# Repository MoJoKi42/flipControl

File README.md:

# flipControl
Full controller for **BROSE** and **LAWO FlipDot** panels based on STM32 µC. Controllable via RS232, RS485 or 3.3V Serial.
With the DIP switches you can decide between BROSE / LAWO and set more parameters without reprogramming.

<ins>Software/µC:</ins>
- **STM32F103C8Tx** / BluePill Dev-Board
- CubeMX and HAL Libs
- "compile_and_flash.sh" to complile and flash µC under Linux

<ins>Hardware/PCB:</ins>
- PCB + Circuit made with EAGLE 6.6.0
- Gerber Files are in "Gerber.zip"

Picture of the finished board with soldered RS323 interface:

Two different font types are possible (if you render the text with the MCU):

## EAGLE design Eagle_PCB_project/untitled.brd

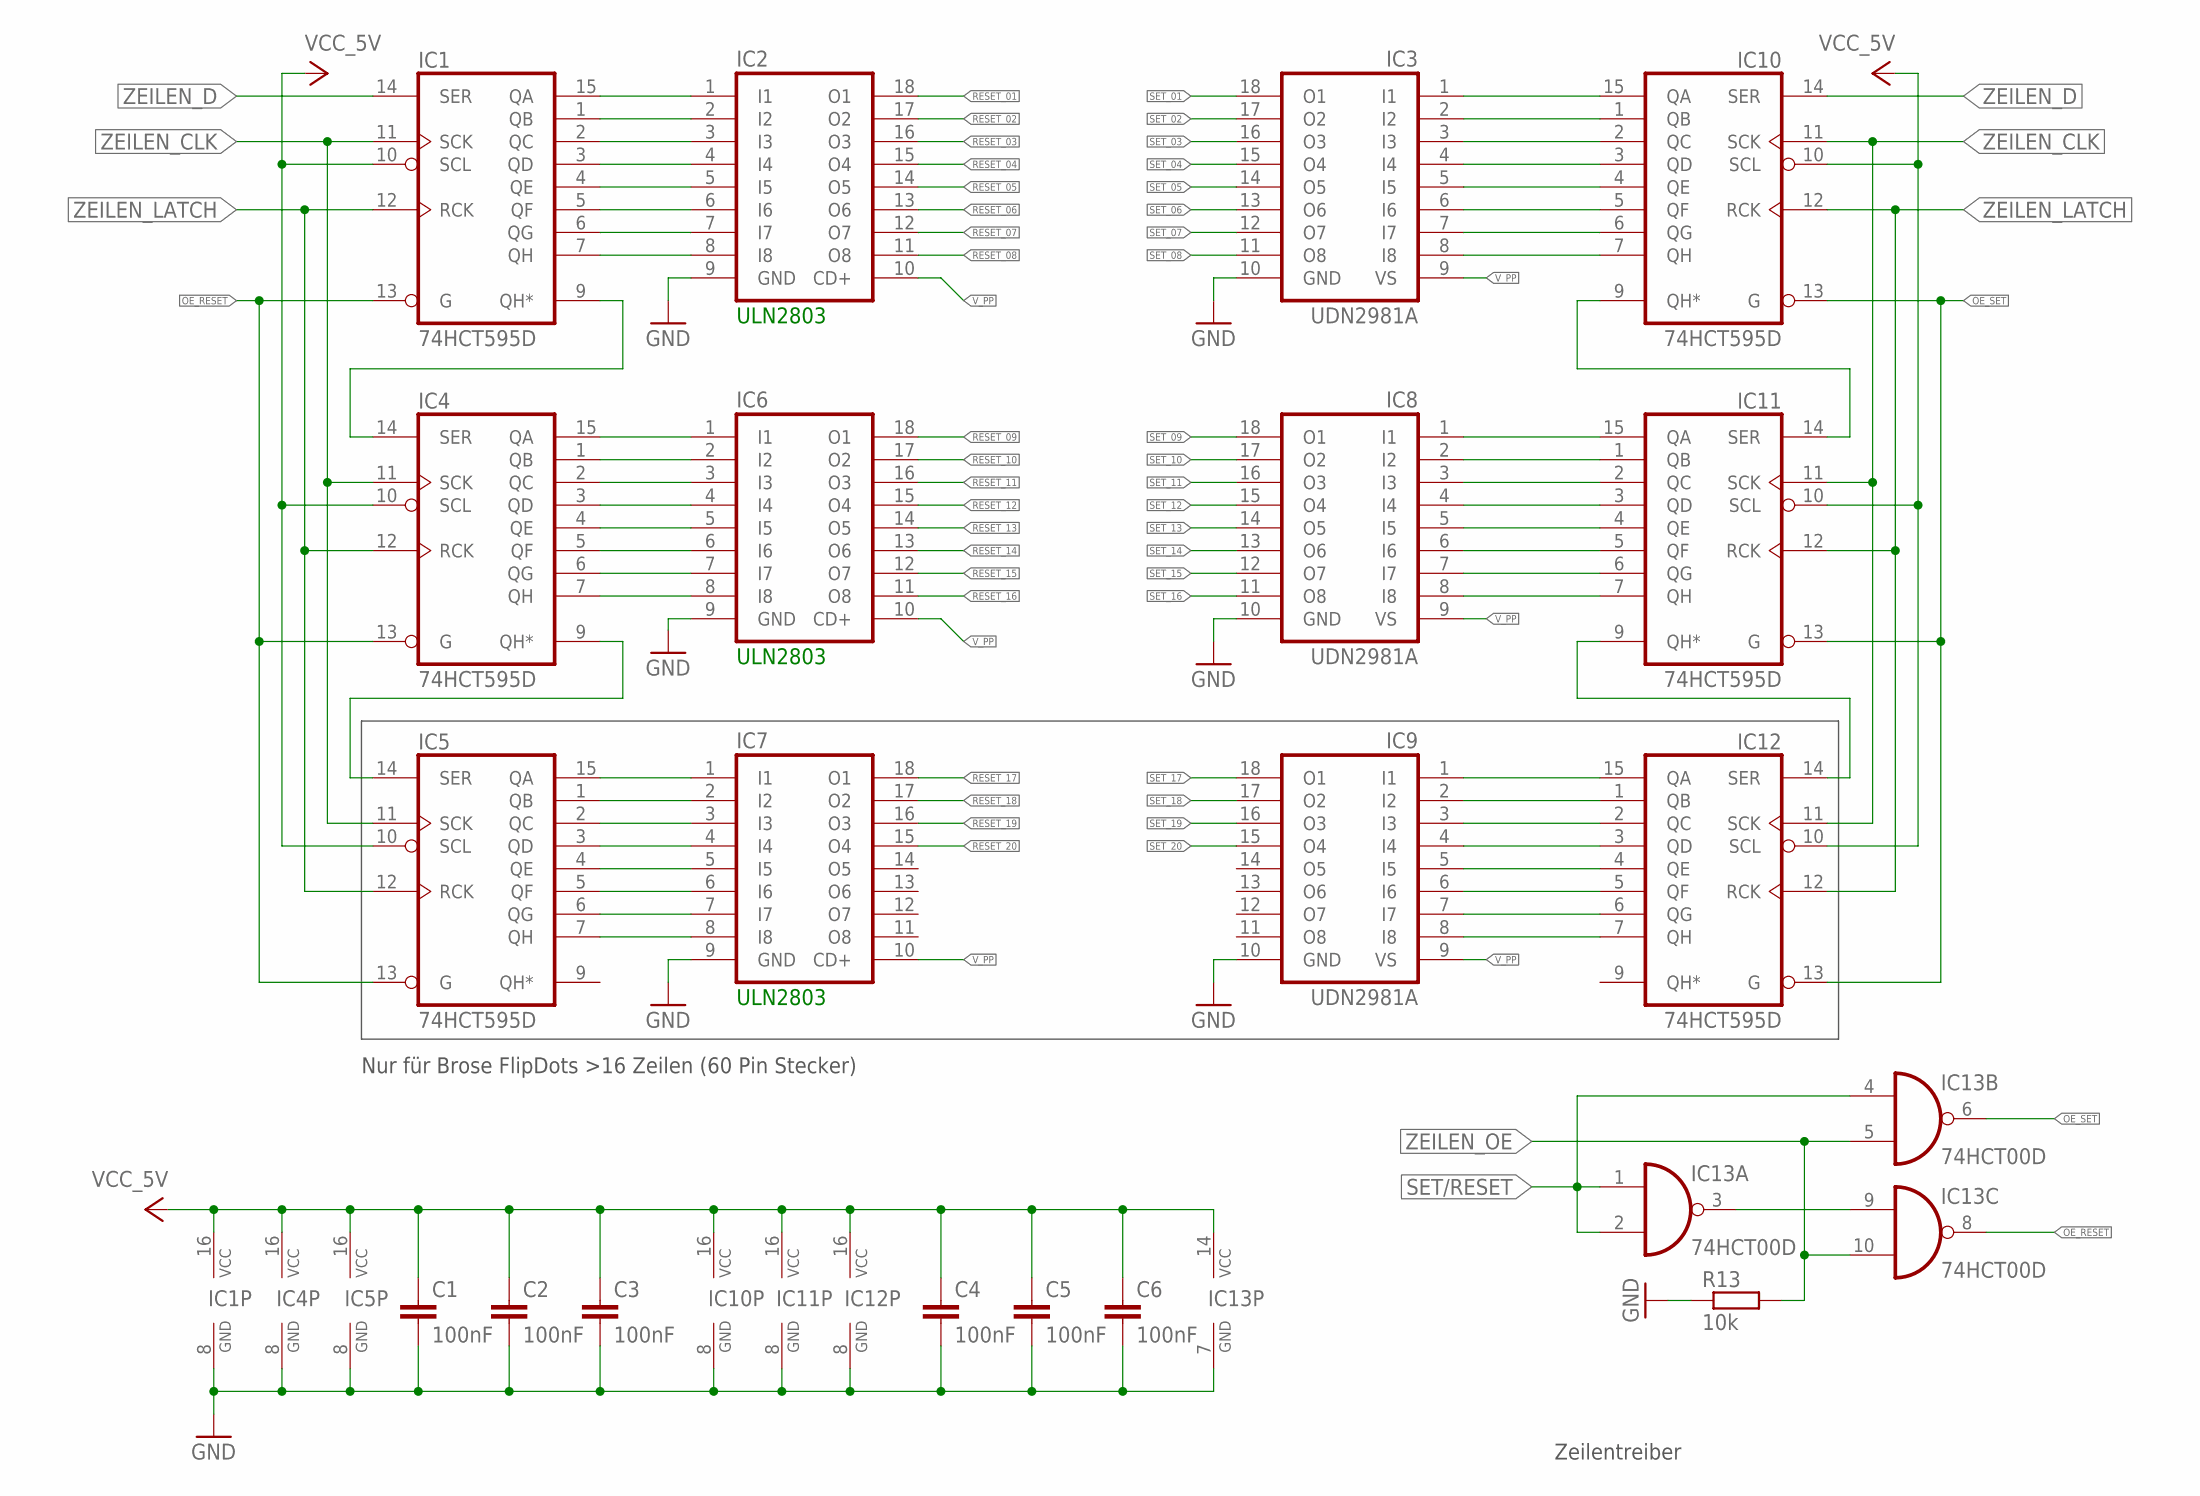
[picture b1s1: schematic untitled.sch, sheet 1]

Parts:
C1, C2, C3, C4, C5, C6: 100nF; C1206K
IC1, IC4, IC5, IC10, IC11, IC12: 74HCT595D; SO16
IC2, IC6, IC7: ULN2803A; DIL18
IC3, IC8, IC9: UDN2981A; DIL18
IC13: 74HCT00D; SO14
R13: 10k; R0805

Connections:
GND: C1.2, C2.2, C3.2, C4.2, C5.2, C6.2, IC1.8 (GND), IC2.9 (GND), IC3.10 (GND), IC4.8 (GND), IC5.8 (GND), IC6.9 (GND), IC7.9 (GND), IC8.10 (GND), IC9.10 (GND), IC10.8 (GND), IC11.8 (GND), IC12.8 (GND), IC13.7 (GND), R13.1; also elsewhere on the board
unnamed: IC1.9 (QH*), IC4.14 (SER)
unnamed: IC4.9 (QH*), IC5.14 (SER)
unnamed: IC4.15 (QA), IC6.1 (I1)
unnamed: IC4.1 (QB), IC6.2 (I2)
unnamed: IC4.2 (QC), IC6.3 (I3)
unnamed: IC4.3 (QD), IC6.4 (I4)
unnamed: IC4.4 (QE), IC6.5 (I5)
unnamed: IC4.5 (QF), IC6.6 (I6)
unnamed: IC4.6 (QG), IC6.7 (I7)
unnamed: IC4.7 (QH), IC6.8 (I8)
unnamed: IC1.15 (QA), IC2.1 (I1)
unnamed: IC1.1 (QB), IC2.2 (I2)
unnamed: IC1.2 (QC), IC2.3 (I3)
unnamed: IC1.3 (QD), IC2.4 (I4)
unnamed: IC1.4 (QE), IC2.5 (I5)
unnamed: IC1.5 (QF), IC2.6 (I6)
unnamed: IC1.6 (QG), IC2.7 (I7)
unnamed: IC1.7 (QH), IC2.8 (I8)
unnamed: IC5.15 (QA), IC7.1 (I1)
unnamed: IC5.1 (QB), IC7.2 (I2)
unnamed: IC5.2 (QC), IC7.3 (I3)
unnamed: IC5.3 (QD), IC7.4 (I4)
unnamed: IC5.4 (QE), IC7.5 (I5)
unnamed: IC5.5 (QF), IC7.6 (I6)
unnamed: IC5.6 (QG), IC7.7 (I7)
unnamed: IC5.7 (QH), IC7.8 (I8)
unnamed: IC3.2 (I2), IC10.1 (QB)
unnamed: IC3.3 (I3), IC10.2 (QC)
unnamed: IC3.4 (I4), IC10.3 (QD)
unnamed: IC3.5 (I5), IC10.4 (QE)
unnamed: IC3.6 (I6), IC10.5 (QF)
unnamed: IC3.7 (I7), IC10.6 (QG)
unnamed: IC3.8 (I8), IC10.7 (QH)
unnamed: IC3.1 (I1), IC10.15 (QA)
unnamed: IC8.2 (I2), IC11.1 (QB)
unnamed: IC8.3 (I3), IC11.2 (QC)
unnamed: IC8.4 (I4), IC11.3 (QD)
unnamed: IC8.5 (I5), IC11.4 (QE)
unnamed: IC8.6 (I6), IC11.5 (QF)
unnamed: IC8.7 (I7), IC11.6 (QG)
unnamed: IC8.8 (I8), IC11.7 (QH)
unnamed: IC8.1 (I1), IC11.15 (QA)
unnamed: IC9.2 (I2), IC12.1 (QB)
unnamed: IC9.3 (I3), IC12.2 (QC)
unnamed: IC9.4 (I4), IC12.3 (QD)
unnamed: IC9.5 (I5), IC12.4 (QE)
unnamed: IC9.6 (I6), IC12.5 (QF)
unnamed: IC9.7 (I7), IC12.6 (QG)
unnamed: IC9.8 (I8), IC12.7 (QH)
unnamed: IC9.1 (I1), IC12.15 (QA)
unnamed: IC10.9 (QH*), IC11.14 (SER)
unnamed: IC11.9 (QH*), IC12.14 (SER)
unnamed: IC13.3 (O), IC13.9 (I0)
OE_RESET: IC1.13 (G), IC4.13 (G), IC5.13 (G), IC13.8 (O)
OE_SET: IC10.13 (G), IC11.13 (G), IC12.13 (G), IC13.6 (O)
RESET_01: IC2.18 (O1); also elsewhere on the board
RESET_02: IC2.17 (O2); also elsewhere on the board
RESET_03: IC2.16 (O3); also elsewhere on the board
RESET_04: IC2.15 (O4); also elsewhere on the board
RESET_05: IC2.14 (O5); also elsewhere on the board
RESET_06: IC2.13 (O6); also elsewhere on the board
RESET_07: IC2.12 (O7); also elsewhere on the board
RESET_08: IC2.11 (O8); also elsewhere on the board
RESET_09: IC6.18 (O1); also elsewhere on the board
RESET_10: IC6.17 (O2); also elsewhere on the board
RESET_11: IC6.16 (O3); also elsewhere on the board
RESET_12: IC6.15 (O4); also elsewhere on the board
RESET_13: IC6.14 (O5); also elsewhere on the board
RESET_14: IC6.13 (O6); also elsewhere on the board
RESET_15: IC6.12 (O7); also elsewhere on the board
RESET_16: IC6.11 (O8); also elsewhere on the board
RESET_17: IC7.18 (O1); also elsewhere on the board
RESET_18: IC7.17 (O2); also elsewhere on the board
RESET_19: IC7.16 (O3); also elsewhere on the board
RESET_20: IC7.15 (O4); also elsewhere on the board
SET/RESET: IC13.1 (I0), IC13.2 (I1), IC13.4 (I0); also elsewhere on the board
SET_01: IC3.18 (O1); also elsewhere on the board
SET_02: IC3.17 (O2); also elsewhere on the board
SET_03: IC3.16 (O3); also elsewhere on the board
SET_04: IC3.15 (O4); also elsewhere on the board
SET_05: IC3.14 (O5); also elsewhere on the board
SET_06: IC3.13 (O6); also elsewhere on the board
SET_07: IC3.12 (O7); also elsewhere on the board
SET_08: IC3.11 (O8); also elsewhere on the board
SET_09: IC8.18 (O1); also elsewhere on the board
SET_10: IC8.17 (O2); also elsewhere on the board
SET_11: IC8.16 (O3); also elsewhere on the board
SET_12: IC8.15 (O4); also elsewhere on the board
SET_13: IC8.14 (O5); also elsewhere on the board
SET_14: IC8.13 (O6); also elsewhere on the board
SET_15: IC8.12 (O7); also elsewhere on the board
SET_16: IC8.11 (O8); also elsewhere on the board
SET_17: IC9.18 (O1); also elsewhere on the board
SET_18: IC9.17 (O2); also elsewhere on the board
SET_19: IC9.16 (O3); also elsewhere on the board
SET_20: IC9.15 (O4); also elsewhere on the board
VCC: C1.1, C2.1, C3.1, C4.1, C5.1, C6.1, IC1.10 (SCL), IC1.16 (VCC), IC4.10 (SCL), IC4.16 (VCC), IC5.10 (SCL), IC5.16 (VCC), IC10.10 (SCL), IC10.16 (VCC), IC11.10 (SCL), IC11.16 (VCC), IC12.10 (SCL), IC12.16 (VCC), IC13.14 (VCC); also elsewhere on the board
V_PP: IC2.10 (CD+), IC3.9 (VS), IC6.10 (CD+), IC7.10 (CD+), IC8.9 (VS), IC9.9 (VS); also elsewhere on the board
ZEILEN_CLK: IC1.11 (SCK), IC4.11 (SCK), IC5.11 (SCK), IC10.11 (SCK), IC11.11 (SCK), IC12.11 (SCK); also elsewhere on the board
ZEILEN_D: IC1.14 (SER), IC10.14 (SER); also elsewhere on the board
ZEILEN_LATCH: IC1.12 (RCK), IC4.12 (RCK), IC5.12 (RCK), IC10.12 (RCK), IC11.12 (RCK), IC12.12 (RCK); also elsewhere on the board
ZEILEN_OE: IC13.5 (I1), IC13.10 (I1), R13.2; also elsewhere on the board

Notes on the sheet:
ULN2803
Nur für Brose FlipDots >16 Zeilen (60 Pin Stecker)
Zeilentreiber

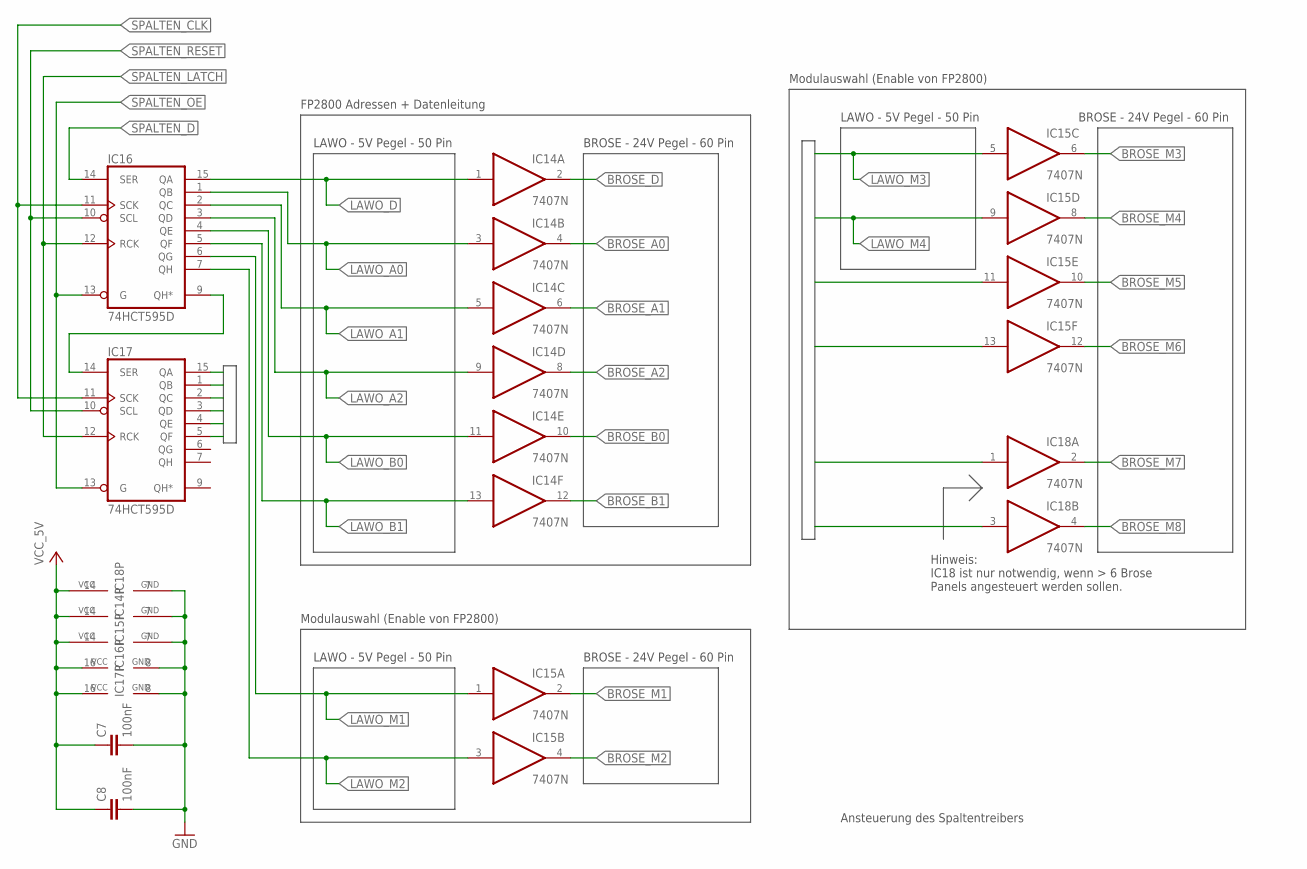
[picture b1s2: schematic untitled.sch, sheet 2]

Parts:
C7, C8: 100nF; C1206K
IC14, IC15, IC18: 7407N; DIL14
IC16, IC17: 74HCT595D; SO16

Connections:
BROSE_A0: IC14.4 (O); also elsewhere on the board
BROSE_A1: IC14.6 (O); also elsewhere on the board
BROSE_A2: IC14.8 (O); also elsewhere on the board
BROSE_B0: IC14.10 (O); also elsewhere on the board
BROSE_B1: IC14.12 (O); also elsewhere on the board
BROSE_D: IC14.2 (O); also elsewhere on the board
BROSE_M1: IC15.2 (O); also elsewhere on the board
BROSE_M2: IC15.4 (O); also elsewhere on the board
BROSE_M3: IC15.6 (O); also elsewhere on the board
BROSE_M4: IC15.8 (O); also elsewhere on the board
BROSE_M5: IC15.10 (O); also elsewhere on the board
BROSE_M6: IC15.12 (O); also elsewhere on the board
BROSE_M7: IC18.2 (O); also elsewhere on the board
BROSE_M8: IC18.4 (O); also elsewhere on the board
GND: C7.2, C8.2, IC14.7 (GND), IC15.7 (GND), IC16.8 (GND), IC17.8 (GND), IC18.7 (GND); also elsewhere on the board
LAWO_A0: IC14.3 (I), IC16.1 (QB); also elsewhere on the board
LAWO_A1: IC14.5 (I), IC16.2 (QC); also elsewhere on the board
LAWO_A2: IC14.9 (I), IC16.3 (QD); also elsewhere on the board
LAWO_B0: IC14.11 (I), IC16.4 (QE); also elsewhere on the board
LAWO_B1: IC14.13 (I), IC16.5 (QF); also elsewhere on the board
LAWO_D: IC14.1 (I), IC16.15 (QA); also elsewhere on the board
LAWO_M1: IC15.1 (I), IC16.6 (QG); also elsewhere on the board
LAWO_M2: IC15.3 (I), IC16.7 (QH); also elsewhere on the board
LAWO_M3: IC15.5 (I), IC17.15 (QA); also elsewhere on the board
LAWO_M4: IC15.9 (I), IC17.1 (QB); also elsewhere on the board
LAWO_M5: IC15.11 (I), IC17.2 (QC)
LAWO_M6: IC15.13 (I), IC17.3 (QD)
LAWO_M7: IC17.4 (QE), IC18.1 (I)
LAWO_M8: IC17.5 (QF), IC18.3 (I)
unnamed: IC16.9 (QH*), IC17.14 (SER)
SPALTEN_CLK: IC16.11 (SCK), IC17.11 (SCK); also elsewhere on the board
SPALTEN_D: IC16.14 (SER); also elsewhere on the board
SPALTEN_LATCH: IC16.12 (RCK), IC17.12 (RCK); also elsewhere on the board
SPALTEN_OE: IC16.13 (G), IC17.13 (G); also elsewhere on the board
SPALTEN_RESET: IC16.10 (SCL), IC17.10 (SCL); also elsewhere on the board
VCC: C7.1, C8.1, IC14.14 (VCC), IC15.14 (VCC), IC16.16 (VCC), IC17.16 (VCC), IC18.14 (VCC); also elsewhere on the board

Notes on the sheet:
LAWO - 5V Pegel - 50 Pin
BROSE - 24V Pegel - 60 Pin
FP2800 Adressen + Datenleitung
Modulauswahl (Enable von FP2800)
Hinweis: IC18 ist nur notwendig, wenn > 6 Brose Panels angesteuert werden sollen.
Ansteuerung des Spaltentreibers

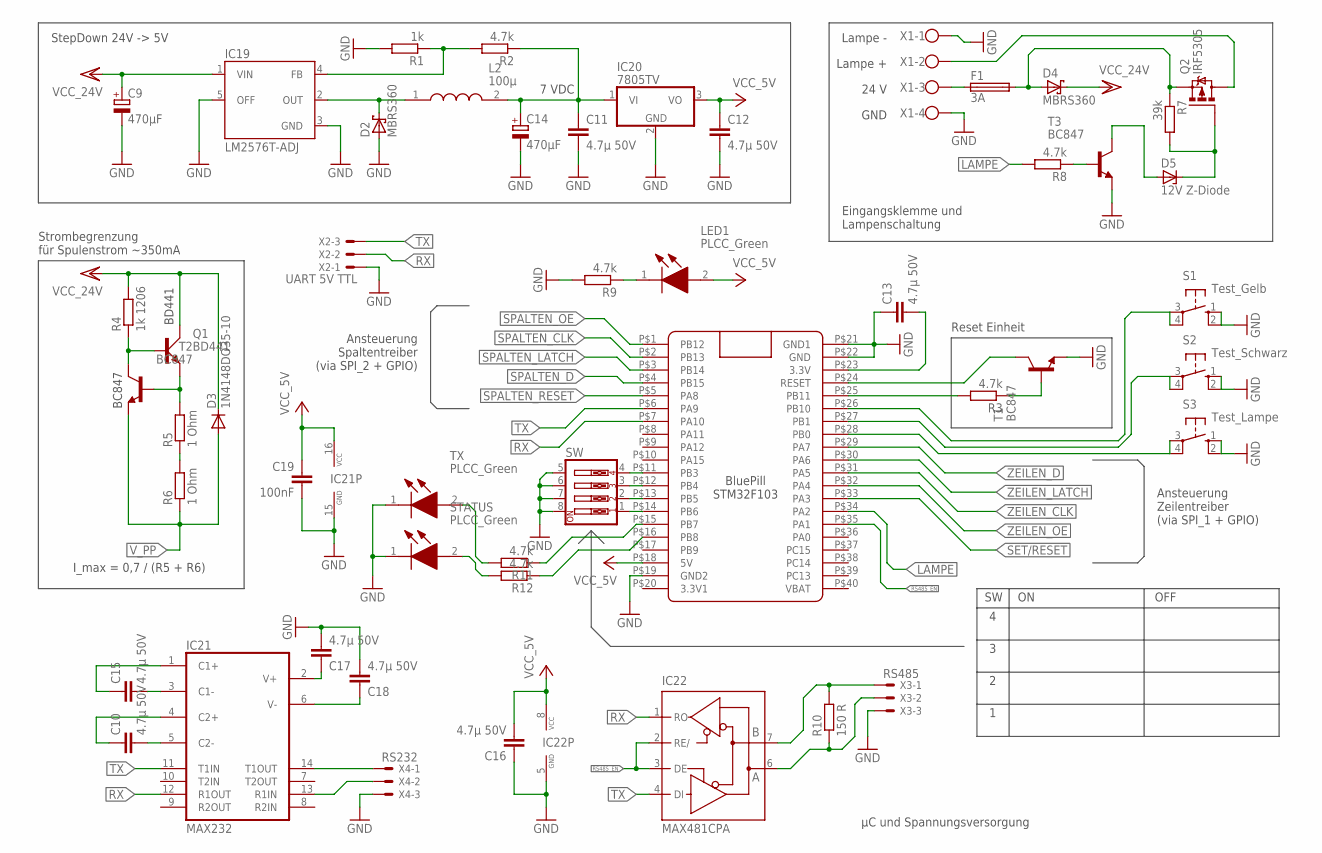
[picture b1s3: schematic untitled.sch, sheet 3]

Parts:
C9, C14: 470µF; E5-10,5
C10, C11, C12, C13, C15, C16, C17, C18: 4.7µ 50V; C1210K
C19: 100nF; C1206K
D2, D4: MBRS360; SMC
D3: 1N4148DO35-10; DO35-10
D5: 12V Z-Diode; SOD80C
F1: 3A; SH22,5
IC19: LM2576T-ADJ; TO220-5
IC20: 7805TV; TO220V
IC21: MAX232; DIL16
IC22: MAX481CPA; DIL08
L2: 100µ; 09HCP121M50
LED1: PLCC_Green; LEDM3528X190N
Q1: BD441; TO126AV
Q2: IRF5305; TO220BV
R1: 1k; R0805
R2, R3, R8, R9, R11, R12: 4.7k; R0805
R4: 1k 1206; R1206
R5, R6: 1 Ohm; M1206
R7: 39k; R0805
R10: 150 R; R1206
S1: Test_Gelb; B3F-10XX
S2: Test_Schwarz; B3F-10XX
S3: Test_Lampe; B3F-10XX
STATUS: PLCC_Green; LEDM3528X190N
SW: SW_DIP-4; EDG-04
T1, T2, T3: BC847; SOT23
TX: PLCC_Green; LEDM3528X190N
U$1: BLUE_PILL
X1: W237-4
X2: UART 5V TTL; 22-23-2031
X3: RS485; 22-23-2031
X4: RS232; 22-23-2031

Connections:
GND: C9.-, C11.2, C12.2, C13.1, C14.-, C16.1, C17.2, C18.2, C19.2, D2.A, IC19.3 (GND), IC19.5 (OFF), IC20.2 (GND), IC21.15 (GND), IC22.5 (GND), R1.2, R9.2, S1.1 (S), S1.2 (S1), S2.1 (S), S2.2 (S1), S3.1 (S), S3.2 (S1), STATUS.1 (K), SW.5, SW.6, SW.7, SW.8, T1.2 (E), T3.2 (E), TX.1 (K), U$1.P$19 (GND2), U$1.P$21 (GND1), U$1.P$22 (GND), X1.1, X1.4, X2.1, X3.3, X4.3; also elsewhere on the board
LAMPE: R8.2, U$1.P$34 (PA2)
unnamed: R5.1, R6.2
unnamed: D5.A, T3.3 (C)
unnamed: F1.1, X1.3
unnamed: D5.C, Q2.G, R7.2
unnamed: D4.A, F1.2, Q2.S, R7.1
unnamed: R8.1, T3.1 (B)
unnamed: SW.1, U$1.P$14 (PB6)
unnamed: SW.2, U$1.P$13 (PB5)
unnamed: SW.3, U$1.P$12 (PB4)
unnamed: SW.4, U$1.P$11 (PB3)
unnamed: LED1.1 (K), R9.1
unnamed: IC22.6 (A), R10.1, X3.2
unnamed: IC22.7 (B), R10.2, X3.1
unnamed: C10.2, IC21.5 (C2-)
unnamed: C10.1, IC21.4 (C2+)
unnamed: IC21.14 (T1OUT), X4.1
unnamed: C15.2, IC21.3 (C1-)
unnamed: C15.1, IC21.1 (C1+)
unnamed: IC21.13 (R1IN), X4.2
unnamed: C17.1, IC21.2 (V+)
unnamed: C18.1, IC21.6 (V-)
unnamed: Q2.D, X1.2
unnamed: R11.1, U$1.P$15 (PB7)
unnamed: R12.1, U$1.P$16 (PB8)
unnamed: R12.2, STATUS.2 (A)
unnamed: R11.2, TX.2 (A)
unnamed: C11.1, C14.+, IC20.1 (VI), L2.2, R2.1
unnamed: D2.C, IC19.2 (OUT), L2.1
unnamed: IC19.4 (FB), R1.1, R2.2
unnamed: R3.1, T1.1 (B)
unnamed: T1.3 (C), U$1.P$24 (RESET)
unnamed: R3.2, U$1.P$25 (PB11)
unnamed: Q1.B, R4.1, T2.3 (C)
unnamed: Q1.E, R5.2, T2.1 (B)
unnamed: S2.3, S2.4 (P1), U$1.P$27 (PB1)
unnamed: S1.3, S1.4 (P1), U$1.P$26 (PB10)
unnamed: S3.3, S3.4 (P1), U$1.P$28 (PB0)
unnamed: C13.2, U$1.P$23 (3.3V)
RS485_EN: IC22.2 (RE/), IC22.3 (DE), U$1.P$35 (PA1)
RX: IC21.12 (R1OUT), IC22.1 (RO), U$1.P$7 (PA10), X2.2
SET/RESET: U$1.P$33 (PA3); also elsewhere on the board
SPALTEN_CLK: U$1.P$2 (PB13); also elsewhere on the board
SPALTEN_D: U$1.P$4 (PB15); also elsewhere on the board
SPALTEN_LATCH: U$1.P$3 (PB14); also elsewhere on the board
SPALTEN_OE: U$1.P$1 (PB12); also elsewhere on the board
SPALTEN_RESET: U$1.P$5 (PA8); also elsewhere on the board
TX: IC21.11 (T1IN), IC22.4 (DI), U$1.P$6 (PA9), X2.3
VCC: C12.1, C16.2, C19.1, IC20.3 (VO), IC21.16 (VCC), IC22.8 (VCC), LED1.2 (A), U$1.P$18 (5V); also elsewhere on the board
VCC/2: C9.+, D3.C, D4.C, IC19.1 (VIN), Q1.C, R4.2; also elsewhere on the board
V_PP: D3.A, R6.1, T2.2 (E); also elsewhere on the board
ZEILEN_CLK: U$1.P$31 (PA5); also elsewhere on the board
ZEILEN_D: U$1.P$29 (PA7); also elsewhere on the board
ZEILEN_LATCH: U$1.P$30 (PA6); also elsewhere on the board
ZEILEN_OE: U$1.P$32 (PA4); also elsewhere on the board

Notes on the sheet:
7 VDC
Reset Einheit
BC847
BD441
Strombegrenzung für Spulenstrom ~350mA
µC und Spannungsversorgung
I_max = 0,7 / (R5 + R6)
StepDown 24V -> 5V
GND
24 V
Lampe +
Lampe -
Eingangsklemme und Lampenschaltung
Ansteuerung Zeilentreiber (via SPI_1 + GPIO)
Ansteuerung Spaltentreiber (via SPI_2 + GPIO)
OFF
BluePill STM32F103

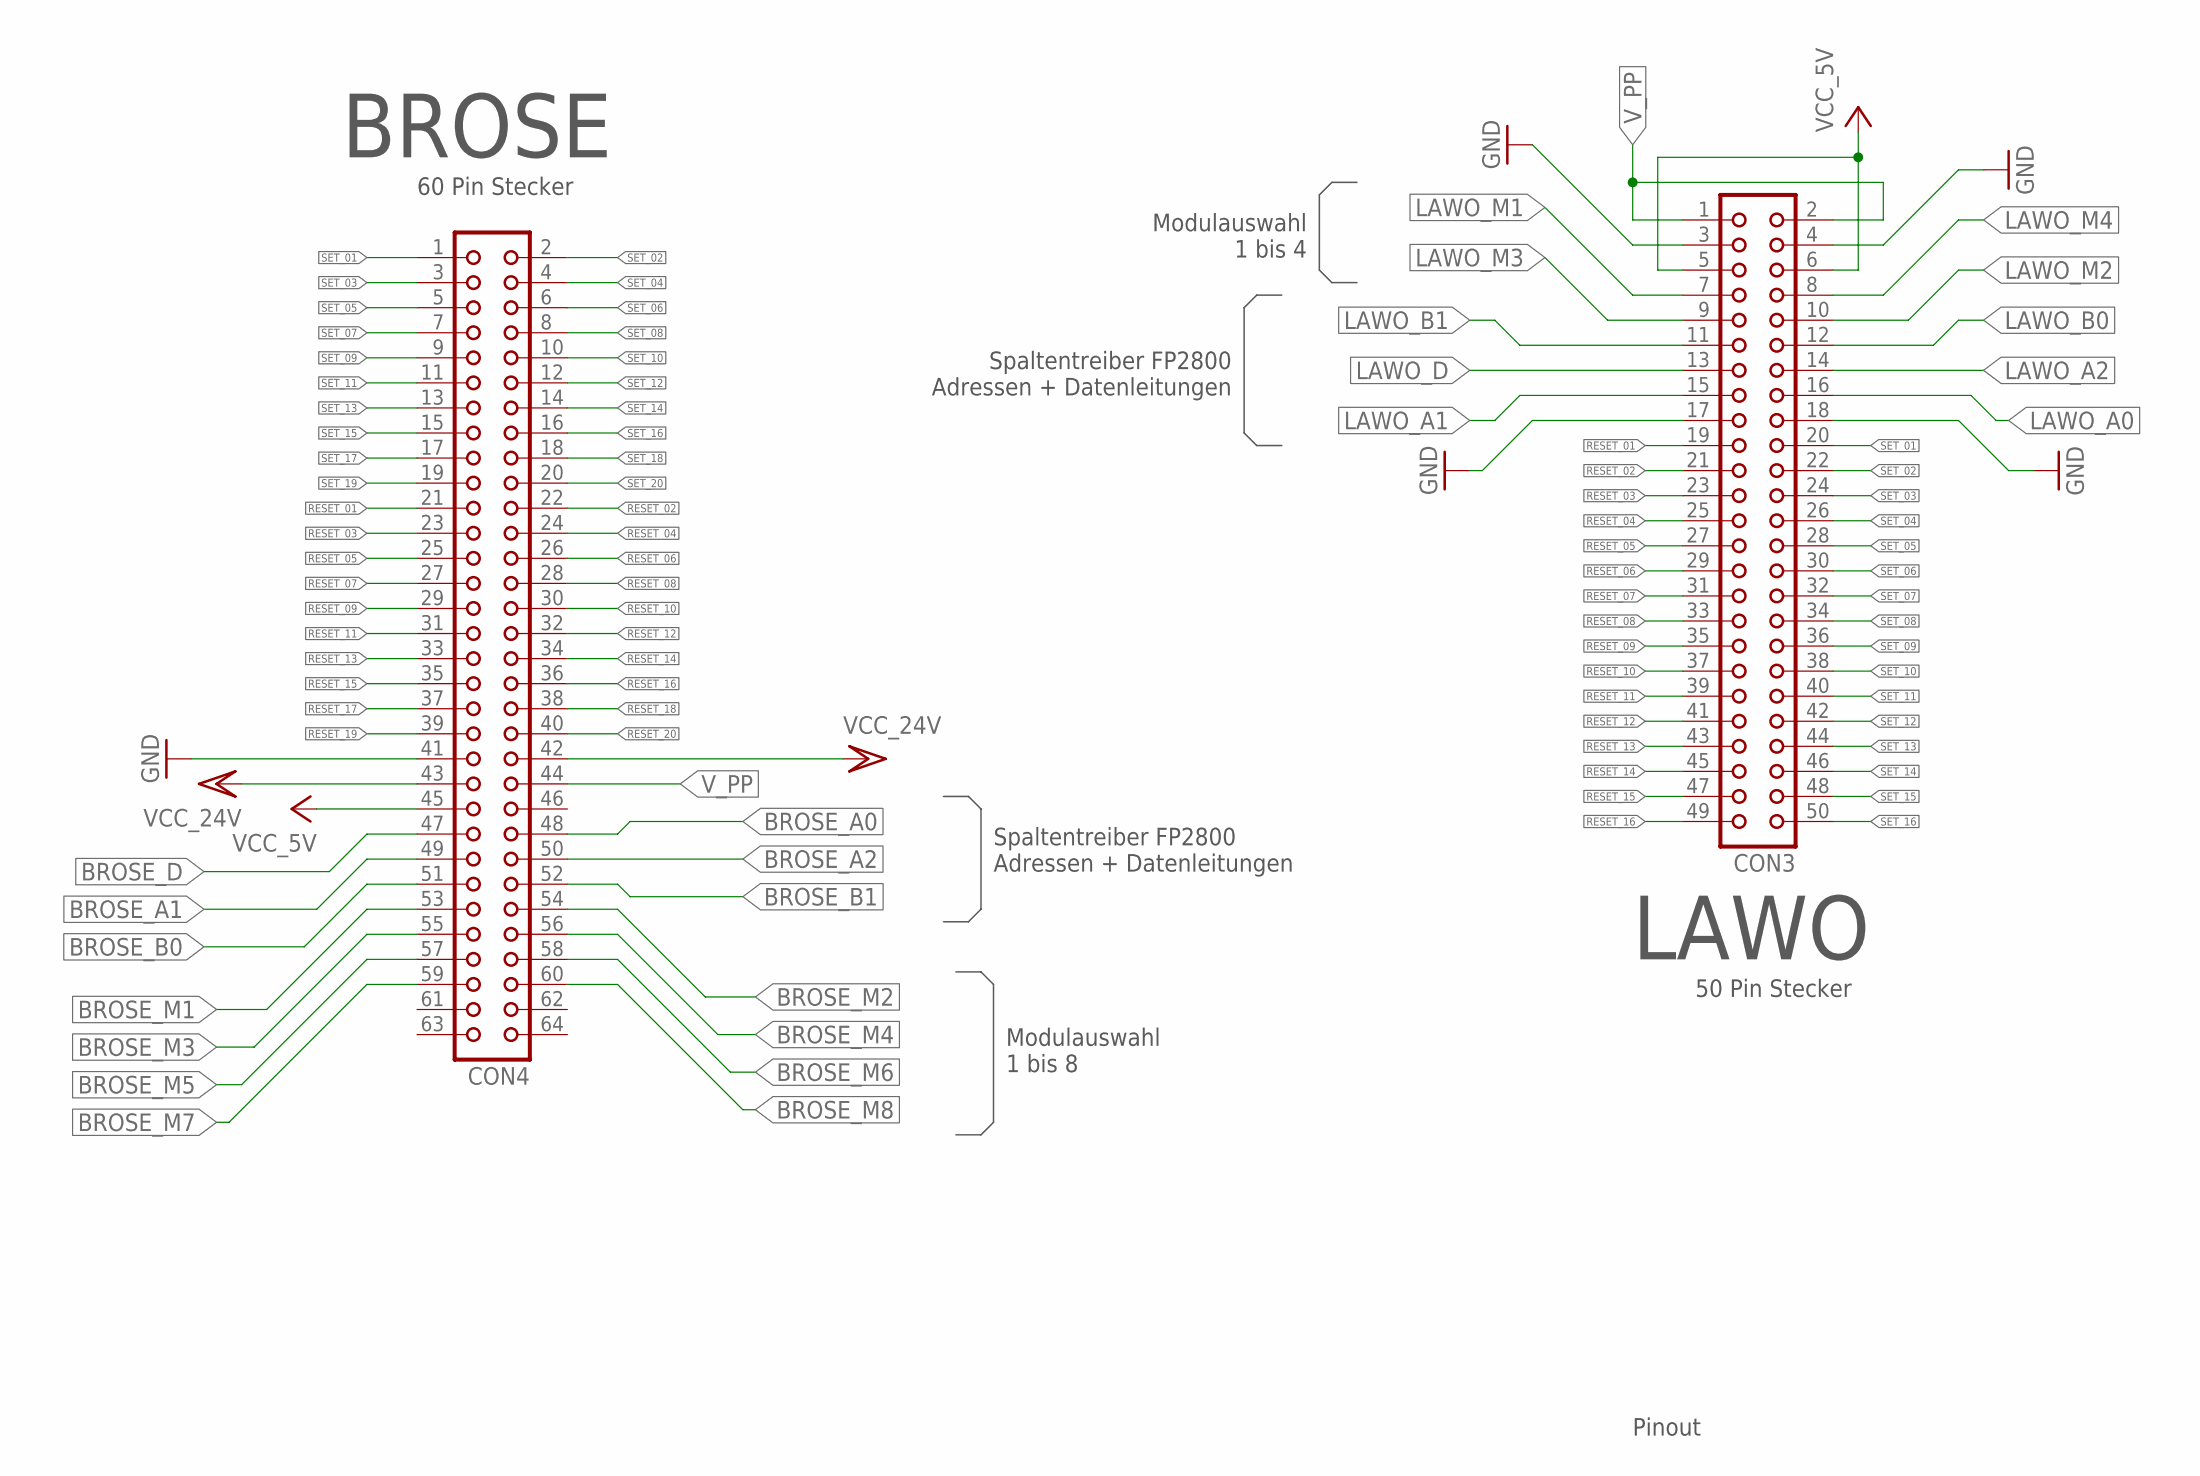
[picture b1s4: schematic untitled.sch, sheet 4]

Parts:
CON3: CON50
CON4: CON64

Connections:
BROSE_A0: CON4.48; also elsewhere on the board
BROSE_A1: CON4.49; also elsewhere on the board
BROSE_A2: CON4.50; also elsewhere on the board
BROSE_B0: CON4.51; also elsewhere on the board
BROSE_B1: CON4.52; also elsewhere on the board
BROSE_D: CON4.47; also elsewhere on the board
BROSE_M1: CON4.53; also elsewhere on the board
BROSE_M2: CON4.54; also elsewhere on the board
BROSE_M3: CON4.55; also elsewhere on the board
BROSE_M4: CON4.56; also elsewhere on the board
BROSE_M5: CON4.57; also elsewhere on the board
BROSE_M6: CON4.58; also elsewhere on the board
BROSE_M7: CON4.59; also elsewhere on the board
BROSE_M8: CON4.60; also elsewhere on the board
GND: CON3.3, CON3.4, CON3.17, CON3.18, CON4.41; also elsewhere on the board
LAWO_A0: CON3.16; also elsewhere on the board
LAWO_A1: CON3.15; also elsewhere on the board
LAWO_A2: CON3.14; also elsewhere on the board
LAWO_B0: CON3.12; also elsewhere on the board
LAWO_B1: CON3.11; also elsewhere on the board
LAWO_D: CON3.13; also elsewhere on the board
LAWO_M1: CON3.7; also elsewhere on the board
LAWO_M2: CON3.10; also elsewhere on the board
LAWO_M3: CON3.9; also elsewhere on the board
LAWO_M4: CON3.8; also elsewhere on the board
RESET_01: CON3.19, CON4.21; also elsewhere on the board
RESET_02: CON3.21, CON4.22; also elsewhere on the board
RESET_03: CON3.23, CON4.23; also elsewhere on the board
RESET_04: CON3.25, CON4.24; also elsewhere on the board
RESET_05: CON3.27, CON4.25; also elsewhere on the board
RESET_06: CON3.29, CON4.26; also elsewhere on the board
RESET_07: CON3.31, CON4.27; also elsewhere on the board
RESET_08: CON3.33, CON4.28; also elsewhere on the board
RESET_09: CON3.35, CON4.29; also elsewhere on the board
RESET_10: CON3.37, CON4.30; also elsewhere on the board
RESET_11: CON3.39, CON4.31; also elsewhere on the board
RESET_12: CON3.41, CON4.32; also elsewhere on the board
RESET_13: CON3.43, CON4.33; also elsewhere on the board
RESET_14: CON3.45, CON4.34; also elsewhere on the board
RESET_15: CON3.47, CON4.35; also elsewhere on the board
RESET_16: CON3.49, CON4.36; also elsewhere on the board
RESET_17: CON4.37; also elsewhere on the board
RESET_18: CON4.38; also elsewhere on the board
RESET_19: CON4.39; also elsewhere on the board
RESET_20: CON4.40; also elsewhere on the board
SET_01: CON3.20, CON4.1; also elsewhere on the board
SET_02: CON3.22, CON4.2; also elsewhere on the board
SET_03: CON3.24, CON4.3; also elsewhere on the board
SET_04: CON3.26, CON4.4; also elsewhere on the board
SET_05: CON3.28, CON4.5; also elsewhere on the board
SET_06: CON3.30, CON4.6; also elsewhere on the board
SET_07: CON3.32, CON4.7; also elsewhere on the board
SET_08: CON3.34, CON4.8; also elsewhere on the board
SET_09: CON3.36, CON4.9; also elsewhere on the board
SET_10: CON3.38, CON4.10; also elsewhere on the board
SET_11: CON3.40, CON4.11; also elsewhere on the board
SET_12: CON3.42, CON4.12; also elsewhere on the board
SET_13: CON3.44, CON4.13; also elsewhere on the board
SET_14: CON3.46, CON4.14; also elsewhere on the board
SET_15: CON3.48, CON4.15; also elsewhere on the board
SET_16: CON3.50, CON4.16; also elsewhere on the board
SET_17: CON4.17; also elsewhere on the board
SET_18: CON4.18; also elsewhere on the board
SET_19: CON4.19; also elsewhere on the board
SET_20: CON4.20; also elsewhere on the board
VCC: CON3.5, CON3.6, CON4.45; also elsewhere on the board
VCC/2: CON4.42, CON4.43; also elsewhere on the board
V_PP: CON3.1, CON3.2, CON4.44; also elsewhere on the board

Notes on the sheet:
Spaltentreiber FP2800 Adressen + Datenleitungen
Modulauswahl 1 bis 8
Modulauswahl 1 bis 4
Pinout
BROSE
LAWO
60 Pin Stecker
50 Pin Stecker

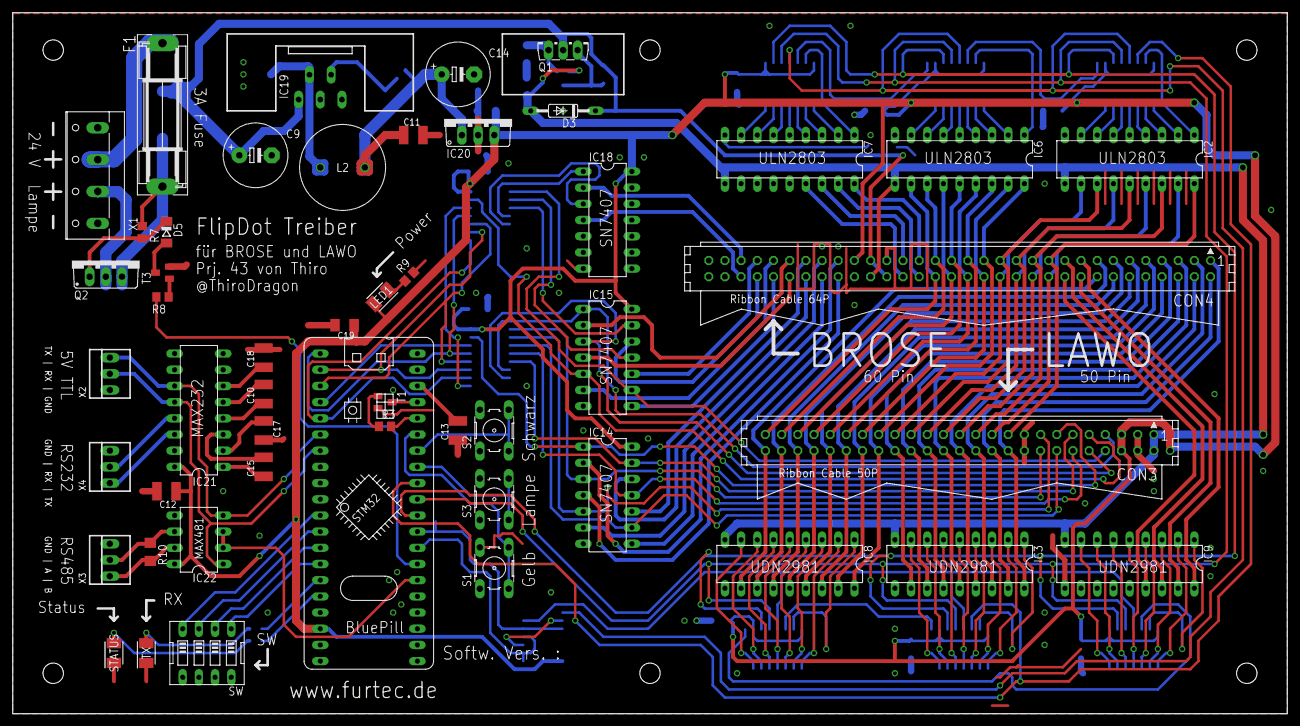
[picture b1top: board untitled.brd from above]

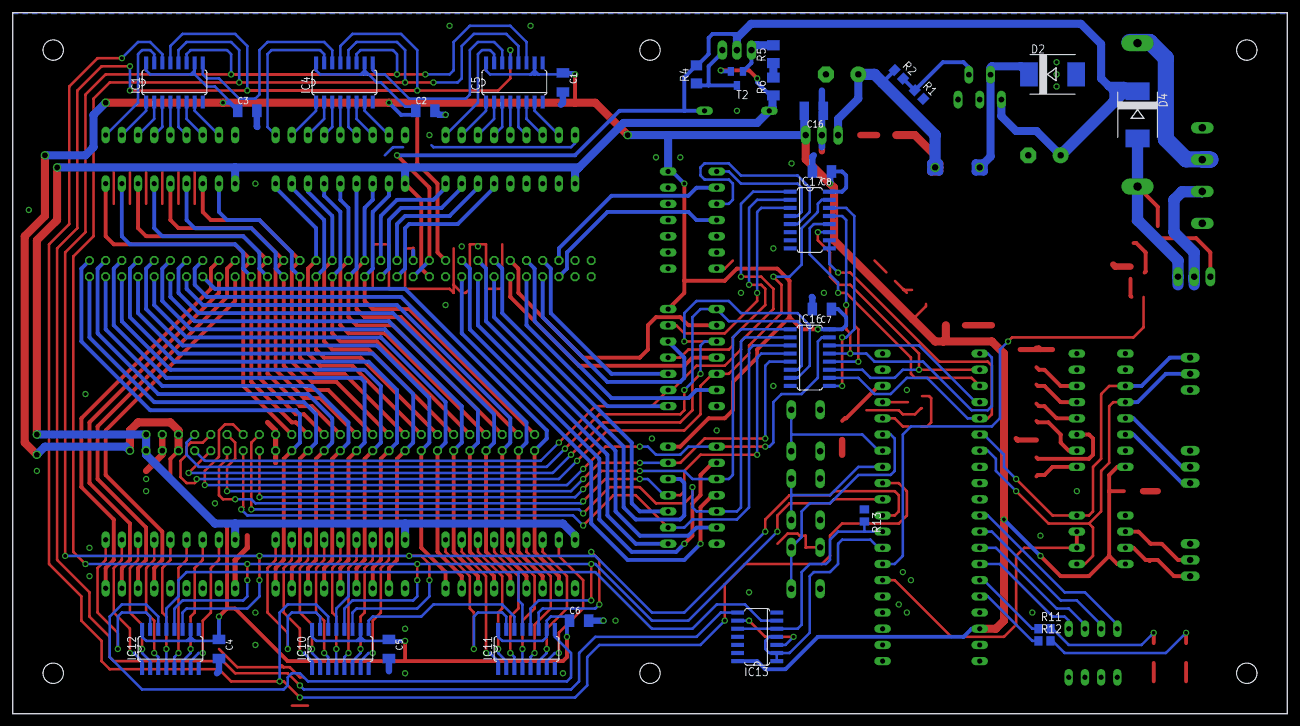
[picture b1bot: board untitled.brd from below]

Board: 2 copper layers, 200.0 x 110.0 mm, 79 parts (29 on the bottom side), 180 nets.

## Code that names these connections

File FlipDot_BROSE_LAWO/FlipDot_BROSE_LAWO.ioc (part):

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Mcu.Name=STM32F103C(8-B)Tx
Mcu.Package=LQFP48
Mcu.UserName=STM32F103C8Tx
PA1.GPIOParameters=GPIO_Label
PA1.GPIO_Label=RS485_EN
PA1.Signal=GPIO_Output
PA10.GPIOParameters=GPIO_PuPd
PA10.GPIO_PuPd=GPIO_PULLUP
PA10.Mode=Asynchronous
PA10.Signal=USART1_RX
PA13.Mode=Serial_Wire
PA13.Signal=SYS_JTMS-SWDIO
PA14.Mode=Serial_Wire
PA14.Signal=SYS_JTCK-SWCLK
PA2.GPIOParameters=GPIO_Label
PA2.GPIO_Label=Lampe
PA2.Signal=GPIO_Output
PA3.GPIOParameters=GPIO_Label
PA3.GPIO_Label=Zeilen_SET_RESET
PA3.Signal=GPIO_Output
PA4.GPIOParameters=GPIO_Label
PA4.GPIO_Label=Zeilen_OE
PA4.Signal=GPIO_Output
PA5.GPIOParameters=GPIO_Label
PA5.GPIO_Label=Zeilen_CLK
PA5.Mode=TX_Only_Simplex_Unidirect_Master
PA5.Signal=SPI1_SCK
PA6.GPIOParameters=GPIO_Label
PA6.GPIO_Label=Zeilen_LATCH
PA6.Signal=GPIO_Output
PA7.GPIOParameters=GPIO_Label
PA7.GPIO_Label=Zeilen_D
PA7.Mode=TX_Only_Simplex_Unidirect_Master
PA7.Signal=SPI1_MOSI
PA8.GPIOParameters=GPIO_Label
PA8.GPIO_Label=Spalten_RESET
PA8.Signal=GPIO_Output
PA9.Mode=Asynchronous
PA9.Signal=USART1_TX
PB0.GPIOParameters=GPIO_PuPd,GPIO_Label
PB0.GPIO_Label=Test_Lampe
PB0.GPIO_PuPd=GPIO_PULLUP
PB0.Signal=GPIO_Input
PB1.GPIOParameters=GPIO_PuPd,GPIO_Label
PB1.GPIO_Label=Test_Schwarz
PB1.GPIO_PuPd=GPIO_PULLUP
PB1.Signal=GPIO_Input
PB10.GPIOParameters=GPIO_PuPd,GPIO_Label
PB10.GPIO_Label=Test_Gelb
PB10.GPIO_PuPd=GPIO_PULLUP
PB10.Signal=GPIO_Input
PB11.GPIOParameters=GPIO_Label
PB11.GPIO_Label=Reset
PB11.Signal=GPIO_Output
PB12.GPIOParameters=GPIO_Label
PB12.GPIO_Label=Spalten_OE
PB12.Signal=GPIO_Output
PB13.GPIOParameters=GPIO_Label
PB13.GPIO_Label=Spalten_CLK
PB13.Mode=TX_Only_Simplex_Unidirect_Master
PB13.Signal=SPI2_SCK
PB14.GPIOParameters=GPIO_Label
PB14.GPIO_Label=Spalten_LATCH
PB14.Signal=GPIO_Output
PB15.GPIOParameters=GPIO_Label
PB15.GPIO_Label=Spalten_D
PB15.Mode=TX_Only_Simplex_Unidirect_Master
PB15.Signal=SPI2_MOSI
PB3.GPIOParameters=GPIO_PuPd,GPIO_Label
PB3.GPIO_Label=SW_4
PB3.GPIO_PuPd=GPIO_PULLUP
PB3.Signal=GPIO_Input
PB4.GPIOParameters=GPIO_PuPd,GPIO_Label
PB4.GPIO_Label=SW_3
PB4.GPIO_PuPd=GPIO_PULLUP
PB4.Signal=GPIO_Input
PB5.GPIOParameters=GPIO_PuPd,GPIO_Label
PB5.GPIO_Label=SW_2
PB5.GPIO_PuPd=GPIO_PULLUP
PB5.Signal=GPIO_Input
PB6.GPIOParameters=GPIO_PuPd,GPIO_Label
PB6.GPIO_Label=SW_1
PB6.GPIO_PuPd=GPIO_PULLUP
PB6.Signal=GPIO_Input
PB7.GPIOParameters=GPIO_Label
PB7.GPIO_Label=LED_RX
PB7.Signal=GPIO_Output
PB8.GPIOParameters=GPIO_Label
PB8.GPIO_Label=LED_Status
PB8.Signal=GPIO_Output
PC13-TAMPER-RTC.GPIOParameters=GPIO_Label
PC13-TAMPER-RTC.GPIO_Label=OnboardLED
PC13-TAMPER-RTC.Signal=GPIO_Output
PC14-OSC32_IN.Mode=LSE-External-Oscillator
PC14-OSC32_IN.Signal=RCC_OSC32_IN
PC15-OSC32_OUT.Mode=LSE-External-Oscillator
PC15-OSC32_OUT.Signal=RCC_OSC32_OUT
PD0-OSC_IN.Mode=HSE-External-Oscillator
PD0-OSC_IN.Signal=RCC_OSC_IN
PD1-OSC_OUT.Mode=HSE-External-Oscillator
PD1-OSC_OUT.Signal=RCC_OSC_OUT
RCC.SYSCLKFreq_VALUE=72000000
RCC.SYSCLKSource=RCC_SYSCLKSOURCE_PLLCLK
board=custom

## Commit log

2023-01-18 added all files
2023-03-30 fixed pcb mistake
